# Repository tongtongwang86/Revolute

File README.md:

# Revolute
- nRF52833 Based Scroll wheel dial

## Introducing Revolute
 <a href="https://tongtonginc.com/revolute">Visit the product page website (Faster loading time, Interactive 3D Models, Demo Videos)</a>

### The Revolute is a scroll wheel/dial that aims to revolutionize the way we interact with complex software applications.

- Revolute currently simulate keyboard inputs, consumer controlls, mouse inputs.

- the actions and sensitivity of the wheel can be configured through the revolute configurator app that will be available for iOS, Macos and Windows devices that have bluetooth support.

- Configuratios done on revolute is persistently stored on device, which means that revolute can work on any device with Bluetooth and HID support.

- Revolute has a number of use cases and is not limited to: scrubbing through a timeline in a video editing app, changing the brush size in 3D/2D painting, smooth scrolling, volume controll, brightness control, media playback control, quickly pressing keys in short successions within games. if you get two you can bind each revolute axis to x and y of the cursor, making a etch a sketch

- Gamepad emulation is currently in development, which will allow you to use revolute within a wide range of mobile and console games.

## How the Revolute works

### Rotational inputs

- Revolute has gone through a number of iterations and currently uses the AS5600 magnetic encoder. It recordes the angle of a diametric magnet embedded within the base of the revolute, which the SoC will process and send bluetooth reports to the host device.

### BLE connection

- Using BLE wireless connection we can have the Revolute connected to devices such as your computer, phone, or tablet using bluetooth. 
- By using the nRF52833 SoC and Zephyr RTOS, the Revolute is designed to maximize its power efficiency for bluetooth functionalities.

### Central button
- By pressing down on the Revolute, it powers on the device.
- After powering on the device, the button can also be configured to other actions based on your configurations
- Power it off by pressing and holding down on the button.

### Configuration

- As mentioned before, the Revolute's functionalities can be configured through the Revolute Configuration app that is currently in development
- Once you have made your changes to our configurations, they are then sent to the Revolute over bluetooth and stored locally on the SoC. allowing you to use the same configurations across different devices.

### Accessories 
- Revolute has a range of existing accessories that allow you to use it within different use cases

- Key attachment 

- Adhesive/magnetic attachment

- Phone attachment 

- Revo-Pod charges the revolute and is a place to store your attachments.

- The attachment can be hot swapped with a common bearing interface.

### Charging and Battery Replacement
- For this device to be wireless, the Revolute is comprised of a 70Mah li-Ion rechargable coin cell battery (LIR2032H)
- The Revolute uses the BQ24075-RGT charger ic and BQ27441-G1 fuel gauge, both by Texas Instruments, for charging, monitoring, and managing the battery that powers the system.
- To charge the Revolute, simply take your Revopod and mount it in the pod and have the two pogopins aligned with the receptors on the wheel.
- To replace the battery, simply flip the Revolute over, press it down until you feel the central button being completely pressed down, and twist it clockwise and you should be able to have the entire Revolute disassembled. From there, simply place a new battery in and reverse the steps of how you disassembled it after your align the cap with the body chassis.

### *Gyro mouse
- With the LSM6DS3 gyroscope accelerometer incorporated in on the Revolute, you can configure it to control the movements of your cursor by moving the Revolute around.
- This feature is still in development and will be finalized shortly in our next firmware updates

## How this repo works
- PCB hardware files are in the folder /Hardware
- 3D printed part files are stored in the folder /3D Prints
- Latest firmware is hosted on the repo <a href="https://github.com/tongtongwang86/revolute-firmware-ci">"revolute-firmware-ci"</a>
- There is also a wired version of the revolute in this repo

## Get your own Revolute
- Revolute is still in development and will be ready soon

 - <a href="https://tongtonginc.com/revolute">For more information head to the product page</a>

- Feel free to DM us if you have any questions or requests

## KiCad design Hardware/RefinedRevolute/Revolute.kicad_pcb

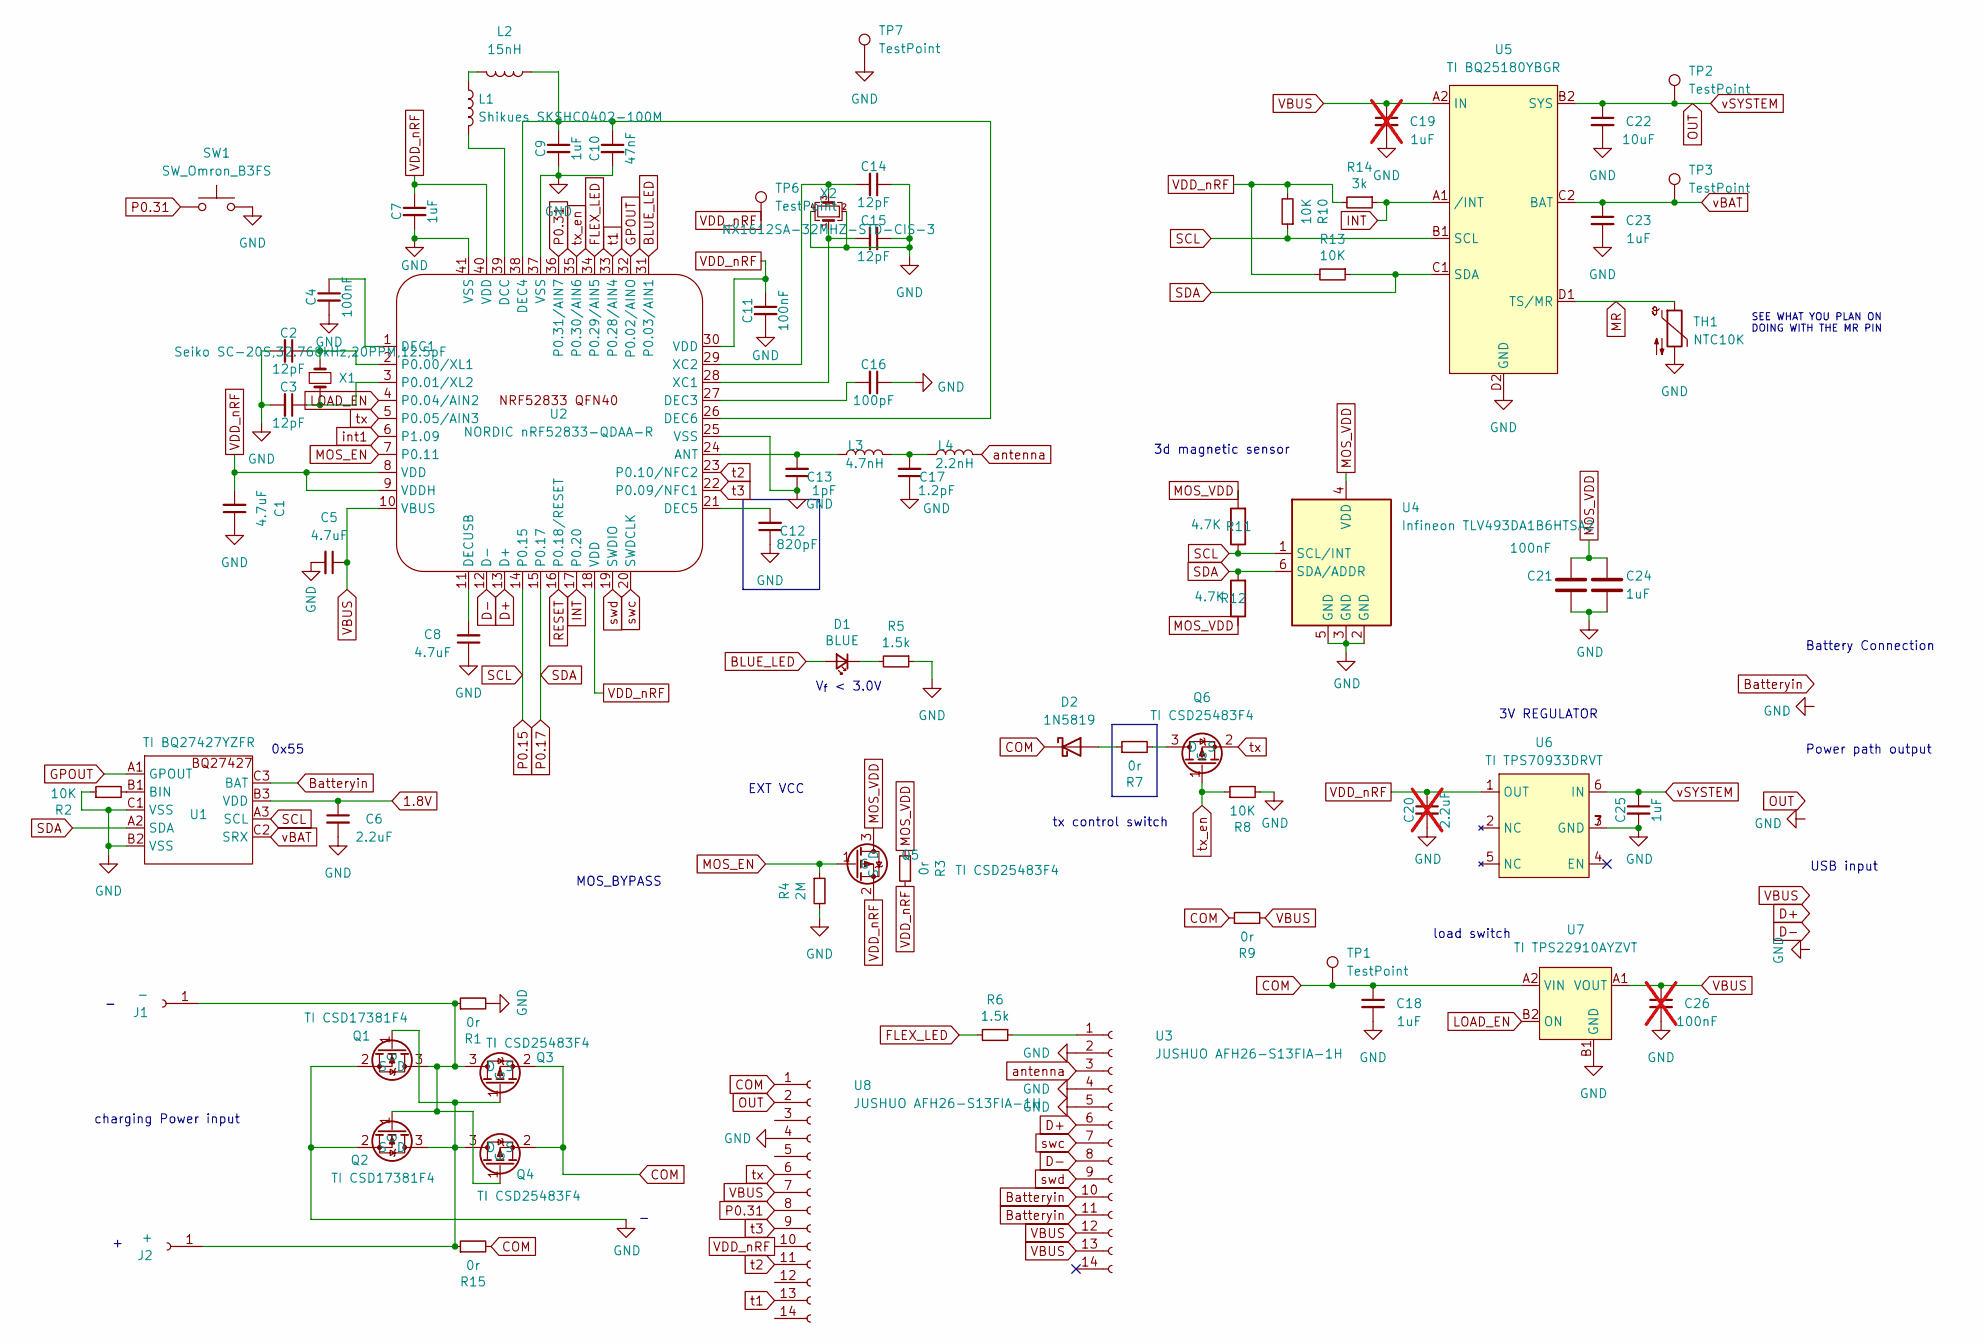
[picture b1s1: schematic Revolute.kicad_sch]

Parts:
C1, C5, C8: 4.7uF; C_0402_1005Metric
C2, C3, C14, C15: 12pF; C_0402_1005Metric
C4, C11, C21: 100nF; C_0402_1005Metric
C6: 2.2uF; C_0402_1005Metric
C7, C9, C18, C23, C24, C25: 1uF; C_0402_1005Metric
C10: 47nF; C_0402_1005Metric
C12: 820pF; C_0402_1005Metric
C13: 1pF; C_0402_1005Metric
C16: 100pF; C_0402_1005Metric
C17: 1.2pF; C_0402_1005Metric
C19: 1uF; C_0402_1005Metric; not fitted
C20: 2.2uF; C_0603_1608Metric; not fitted
C22: 10uF; C_0402_1005Metric
C26: 100nF; C_0402_1005Metric; not fitted
D1: BLUE; LED_0402_1005Metric
D2: 1N5819; D_SOD-523
J1: -; Pogo-pin-recepticle
J2: +; Pogo-pin-recepticle
L1: Shikues SKSHC0402-100M; L_0402_1005Metric; LCSC C18212629
L2: 15nH; L_0402_1005Metric
L3: 4.7nH; L_0402_1005Metric
L4: 2.2nH; L_0402_1005Metric
Q1, Q2: TI CSD17381F4; Mosfet0402; LCSC C2869182
Q3, Q4, Q5, Q6: TI CSD25483F4; Mosfet0402; LCSC C485542
R1, R3, R7, R9, R15: 0r; R_0402_1005Metric
R2, R8, R10, R13: 10K; R_0402_1005Metric
R4: 2M; R_0402_1005Metric
R5, R6: 1.5k; R_0402_1005Metric
R11, R12: 4.7K; R_0402_1005Metric
R14: 3k; R_0402_1005Metric
SW1: SW_Omron_B3FS; 16mmCompButton
TH1: NTC10K; R_0402_1005Metric; LCSC C77131
TP1, TP2, TP3, TP6, TP7: TestPoint; TestPoint_Pad_D1.0mm
U1: TI BQ27427YZFR; Texas_DSBGA-9_1.62mmx1.58mm_Layout3x3_P0.5mm; LCSC C6075475
U2: NORDIC nRF52833-QDAA-R; nrf52833; LCSC C2895249
U3, U8: JUSHUO AFH26-S13FIA-1H; FPC; LCSC C5139786
U4: Infineon TLV493DA1B6HTSA2; SOT-23-6-Small; LCSC C126688
U5: TI BQ25180YBGR; Texas_DSBGA-8_0.705x1.468mm_Layout2x4_P0.4mm; LCSC C3682423
U6: TI TPS70933DRVT; DRV 6PIN; LCSC C2861809
U7: TI TPS22910AYZVT; BGA4N50P2X2_88X88X50N; LCSC C2150034
X1: Seiko SC-20S,32.768kHz,20PPM,12.5pF; Crystal_SMD_2012-2Pin_2.0x1.2mm; LCSC C97607
X2: NX1612SA-32MHZ-STD-CIS-3; Crystal_SMD_2016-4Pin_2.0x1.6mm

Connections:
1.8V: C6.1, U1.B3 (VDD)
BLUE_LED: D1.2 (A), U2.31 (P0.03/AIN1)
Batteryin: U1.C3 (BAT), U3.10, U3.11
COM: C18.1, D2.1 (K), Q3.2 (S), Q4.2 (S), R9.1, R15.2, TP1.1, U7.A2 (VIN), U8.1
D+: U2.13 (D+), U3.6
D-: U2.12 (D-), U3.8
FLEX_LED: R6.2, U2.34 (P0.29/AIN5)
GND: C1.1, C2.2, C3.2, C4.2, C5.2, C6.2, C7.2, C8.1, C9.2, C10.2, C11.2, C12.1, C13.1, C14.1, C15.1, C16.1, C17.1, C18.2, C19.2, C20.2, C21.2, C22.2, C23.2, C24.2, C25.2, C26.2, Q1.2 (S), Q2.2 (S), R1.2, R2.1, R4.2, R5.1, R8.2, SW1.2, TH1.2, TP7.1, U1.B2 (VSS), U1.C1 (VSS), U2.25 (VSS), U2.37 (VSS), U2.41 (VSS), U3.2, U3.4, U3.5, U4.2 (GND), U4.3 (GND), U4.5 (GND), U5.D2 (GND), U6.3 (GND), U6.7 (GND), U7.B1 (GND), U8.4, X2.2, X2.4
GPOUT: U1.A1 (GPOUT), U2.32 (P0.02/AINO)
INT: R14.1, U2.17 (P0.20), U5.A1 (/INT)
LOAD_EN: U2.4 (P0.04/AIN2), U7.B2 (ON)
MOS_EN: Q5.1 (G), R4.1, U2.7 (P0.11)
MOS_VDD: C21.1, C24.1, Q5.3 (D), R3.2, R11.2, R12.1, U4.4 (VDD)
MR: TH1.1, U5.D1 (TS/MR)
unnamed: C17.2, L3.2, L4.1
unnamed: D1.1 (K), R5.2
unnamed: D2.2 (A), R7.1
unnamed: J1.1, Q1.3 (D), Q2.1 (G), Q3.3 (D), Q4.1 (G), R1.1
unnamed: J2.1, Q1.1 (G), Q2.3 (D), Q3.1 (G), Q4.3 (D), R15.1
unnamed: L1.1, L2.2
unnamed: Q6.3 (D), R7.2
unnamed: R2.2, U1.B1 (BIN)
unnamed: C13.2, L3.1, U2.24 (ANT)
unnamed: L1.2, U2.39 (DCC)
unnamed: C4.1, U2.1 (DEC1)
unnamed: C16.2, U2.27 (DEC3)
unnamed: C9.1, C10.1, L2.1, U2.26 (DEC6), U2.38 (DEC4)
unnamed: C12.2, U2.21 (DEC5)
unnamed: C8.2, U2.11 (DECUSB)
unnamed: C2.1, U2.2 (P0.00/XL1), X1.1
unnamed: C3.1, U2.3 (P0.01/XL2), X1.2
unnamed: C15.2, U2.28 (XC1), X2.1
unnamed: C14.2, U2.29 (XC2), X2.3
unnamed: R6.1, U3.1
OUT: C22.1, C25.1, TP2.1, U5.B2 (SYS), U6.6 (IN), U8.2
P0.15: R10.1, R11.1, U1.A3 (SCL), U2.14 (P0.15), U4.1 (SCL/INT), U5.B1 (SCL)
P0.17: R12.2, R13.1, U1.A2 (SDA), U2.15 (P0.17), U4.6 (SDA/ADDR), U5.C1 (SDA)
P0.31: SW1.1, U2.36 (P0.31/AIN7), U8.8
RESET: U2.16 (P0.18/RESET)
VBUS: C5.1, C19.1, C26.1, R9.2, U2.10 (VBUS), U3.12, U3.13, U5.A2 (IN), U7.A1 (VOUT), U8.7
VDD_nRF: C1.2, C7.1, C11.1, C20.1, Q5.2 (S), R3.1, R10.2, R13.2, R14.2, TP6.1, U2.8 (VDD), U2.9 (VDDH), U2.18 (VDD), U2.30 (VDD), U2.40 (VDD), U6.1 (OUT), U8.10
antenna: L4.2, U3.3
int1: U2.6 (P1.09)
swc: U2.20 (SWDCLK), U3.7
swd: U2.19 (SWDIO), U3.9
t1: U2.33 (P0.28/AIN4), U8.13
t2: U2.23 (P0.10/NFC2), U8.11
t3: U2.22 (P0.09/NFC1), U8.9
tx: Q6.2 (S), U2.5 (P0.05/AIN3), U8.6
tx_en: Q6.1 (G), R8.1, U2.35 (P0.30/AIN6)
vBAT: C23.1, TP3.1, U1.C2 (SRX), U5.C2 (BAT)

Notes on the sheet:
3d magnetic sensor
SEE WHAT YOU PLAN ON DOING WITH THE MR PIN
Battery Connection
EXT VCC
Power path output
V_{f} < 3.0V
0x55
charging Power input
USB input
load switch
MOS_BYPASS
tx control switch
3V REGULATOR

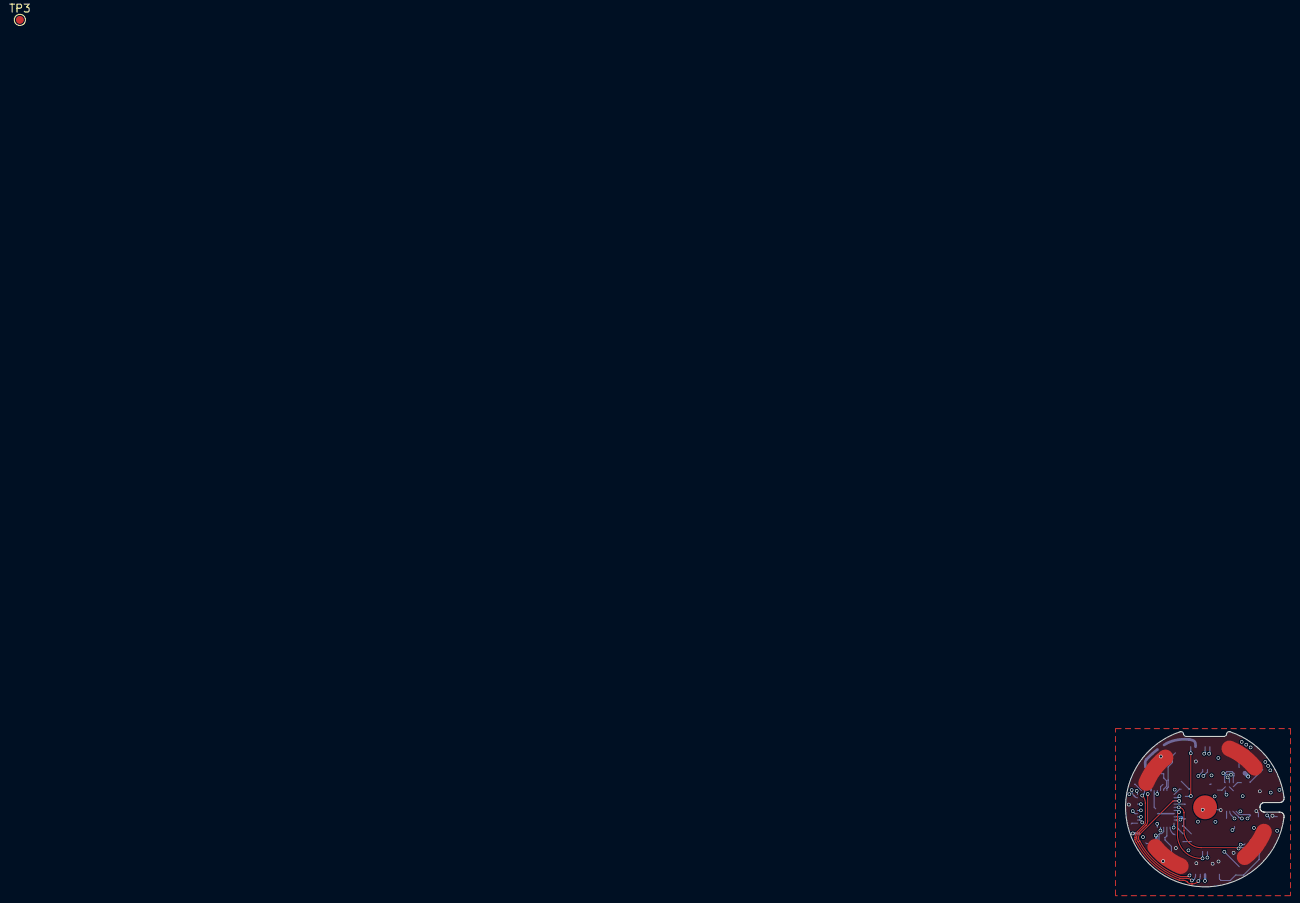
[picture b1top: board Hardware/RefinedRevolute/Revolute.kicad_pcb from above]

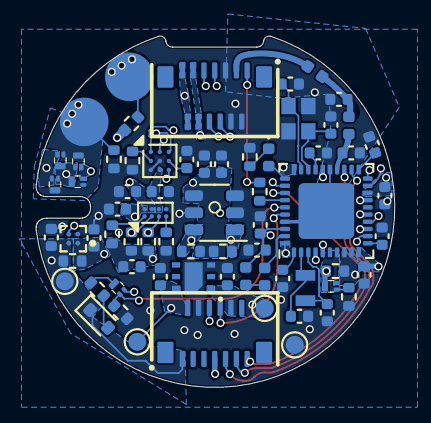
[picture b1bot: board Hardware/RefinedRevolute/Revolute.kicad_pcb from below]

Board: 4 copper layers, 19.9 x 19.5 mm, 71 parts (69 on the bottom side), 49 nets.

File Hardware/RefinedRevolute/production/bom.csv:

Designator,Footprint,Quantity,Value,LCSC Part #
"C1, C5, C8",0402,3,4.7uF,
C10,0402,1,47nF,
"C11, C21, C26, C4",0402,4,100nF,
C12,0402,1,820pF,
C13,0402,1,1pF,
"C14, C15, C2, C3",0402,4,12pF,
C16,0402,1,100pF,
C17,0402,1,1.2pF,
"C18, C19, C23, C24, C25, C7, C9",0402,7,1uF,
C22,0402,1,10uF,
C6,0402,1,2.2uF,
D1,0402,1,BLUE,
D2,D_SOD-523,1,1N5819,
J1,Pogo-pin-recepticle,1,-,
J2,Pogo-pin-recepticle,1,+,
L1,0402,1,10uH,
L2,0402,1,15nH,
L3,0402,1,4.7nH,
L4,0402,1,2.2nH,
"Q1, Q2",Mosfet0402,2,TI CSD17381F4,C2869182
"Q3, Q4, Q5, Q6",Mosfet0402,4,TI CSD25483F4,C485542
"R1, R15, R3, R7, R9",0402,5,0r,
"R10, R13, R2, R8",0402,4,10K,
"R11, R12",0402,2,4.7K,
R14,0402,1,3k,
R4,0402,1,2M,
"R5, R6",0402,2,1.5k,
SW1,16mmCompButton,1,SW_Omron_B3FS,
TH1,0402,1,NTC10K,C77131
"TP1, TP2, TP6, TP7",TestPoint_Pad_D1.0mm,4,TestPoint,
U1,Texas_DSBGA-9_1.62mmx1.58mm_Layout3x3_P0.5mm,1,TI BQ27427YZFR,C6075475
U2,nrf52833,1,NORDIC nRF52833-QDAA-R,C2895249
"U3, U8",FPC,2,JUSHUO AFH26-S13FIA-1H,C5139786
U4,SOT-23-6-Small,1,Infineon TLV493DA1B6HTSA2,C126688
U5,Texas_DSBGA-8_0.705x1.468mm_Layout2x4_P0.4mm,1,TI BQ25180YBGR,C3682423
U6,DRV 6PIN,1,TI TPS70933DRVT,C2861809
U7,BGA4N50P2X2_88X88X50N,1,TI TPS22910AYZVT,C2150034
X1,Crystal_SMD_2012-2Pin_2.0x1.2mm,1,32.768 kHz,
X2,Crystal_SMD_2016-4Pin_2.0x1.6mm,1,32MHZ,

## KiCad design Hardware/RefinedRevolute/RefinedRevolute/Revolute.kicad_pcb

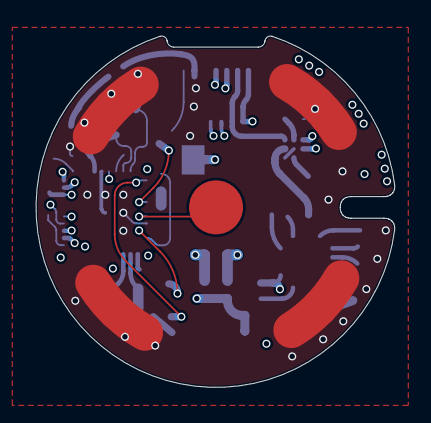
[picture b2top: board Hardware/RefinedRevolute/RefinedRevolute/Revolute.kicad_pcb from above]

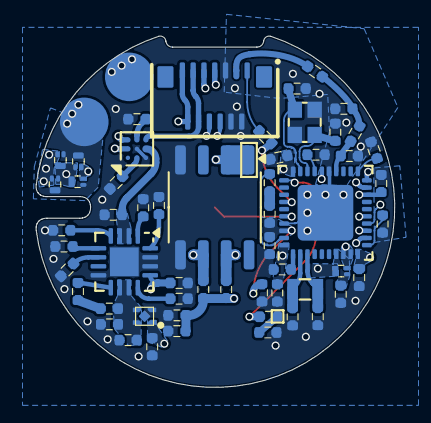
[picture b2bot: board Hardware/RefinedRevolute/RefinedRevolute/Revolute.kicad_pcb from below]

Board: 4 copper layers, 19.9 x 19.5 mm, 59 parts (58 on the bottom side), 45 nets.

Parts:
C1, C5, C7: 4.7uF; 0402
C2, C3, C14, C15: 12pF; 0402
C4, C11, C28: 100nF; 0402
C6, C9, C20, C21, C23, C27: 1uF; 0402
C8: 2.2uF; 0402
C10: 47nF; 0402
C12: 820pF; 0402
C13: 1pF; 0402
C16: 100pF; 0402
C17: 1.2pF; 0402
C22, C24: 10uF; 0402
D1: BLUE; 0402
D2: LED; 0402
J1: -; Pogo-pin-recepticle
J2: +; Pogo-pin-recepticle
L1: 10uH; 0402
L2: 15nH; 0402
L3: 4.7nH; 0402
L4: 2.2nH; 0402
Q1, Q2: NMOS-CSD17381F4; Mosfet0402
Q3, Q4, Q5: PMOS-CSD25483F4; Mosfet0402
R1: 10k; 0402
R2: 2M; 0402
R3, R11, R12: 1.5k; 0402
R4: 100K; 0402
R5: 1.1k; 0402
R6: 590; 0402
R7, R8: 0Ω; 0402
R9, R10: 4.7K; 0402
SW1: SW_Omron_B3FS; 16mmCompButton
TH1: 10K; 0402
U5: BQ27427; Texas_DSBGA-9_1.62mmx1.58mm_Layout3x3_P0.5mm
U6: nrf52833_qfn40; nrf52833
U8: Conn_01x14_Socket; FPC
U9: AS5600; SOIC-8-1EP_3.9x4.9mm_P1.27mm_EP2.514x3.2mm
U10: BQ24075RGT; VQFN-16-1EP_3x3mm_P0.5mm_EP1.6x1.6mm
U11: MIC5504; TDFN-4
X1: 32.768 kHz; Crystal_SMD_2012-2Pin_2.0x1.2mm
X2: 32MHZ; Crystal_SMD_2016-4Pin_2.0x1.6mm

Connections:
1.8V: C8.1, U5.B3 (VDD)
BLUE_LED: D1.2 (A), U6.31 (P0.03/AIN1)
Batteryin: U5.C3 (BAT), U8.10, U8.11
CE: R4.1, U10.4 (~CE)
D+: U6.13 (D+), U8.6
D-: U6.12 (D-), U8.8
FLEX_LED: R12.2, U6.34 (P0.29/AIN5)
GND: C1.1, C2.2, C3.2, C4.2, C5.2, C6.2, C7.1, C8.2, C9.2, C10.2, C11.2, C12.1, C13.1, C14.1, C15.1, C16.1, C17.1, C20.2, C21.2, C22.1, C23.2, C24.2, C27.2, C28.2, Q1.2 (S), Q2.2 (S), R1.1, R2.2, R3.1, R4.2, R5.2, R6.2, R7.1, R8.1, SW1.2, TH1.2, U5.B2 (VSS), U5.C1 (VSS), U6.25 (VSS), U6.37 (VSS), U6.41 (VSS), U8.2, U8.4, U8.5, U9.4 (GND), U9.5 (PGO), U10.8 (VSS), U10.14 (TMR), U10.15 (SYSOFF), U10.17 (VSS), U11.2 (GND), U11.5 (GND), X2.2, X2.4
MOS_EN: Q3.1 (G), R2.1, U6.7 (P0.11)
MOS_VDD: C27.1, C28.1, Q3.3 (D), R9.1, R10.2, U9.1 (VDD5V), U9.2 (VDD3V3)
unnamed: C17.2, L3.2, L4.1
unnamed: D1.1 (K), R3.2
unnamed: D2.1 (K), R11.2
unnamed: J1.1, Q1.3 (D), Q2.1 (G), Q4.3 (D), Q5.1 (G)
unnamed: J2.1, Q1.1 (G), Q2.3 (D), Q4.1 (G), Q5.3 (D)
unnamed: L1.1, L2.2
unnamed: R1.2, U5.B1 (BIN)
unnamed: C13.2, L3.1, U6.24 (ANT)
unnamed: L1.2, U6.39 (DCC)
unnamed: C4.1, U6.1 (DEC1)
unnamed: C16.2, U6.27 (DEC3)
unnamed: C9.1, C10.1, L2.1, U6.26 (DEC6), U6.38 (DEC4)
unnamed: C12.2, U6.21 (DEC5)
unnamed: C7.2, U6.11 (DECUSB)
unnamed: C2.1, U6.2 (P0.00/XL1), X1.1
unnamed: C3.1, U6.3 (P0.01/XL2), X1.2
unnamed: C15.2, U6.28 (XC1), X2.1
unnamed: C14.2, U6.29 (XC2), X2.3
unnamed: R12.1, U8.1
unnamed: R7.2, U10.6 (EN1)
unnamed: R8.2, U10.5 (EN2)
unnamed: R5.1, U10.12 (ILIM)
unnamed: R6.1, U10.16 (ISET)
unnamed: TH1.1, U10.1 (TS)
unnamed: R11.1, U10.9 (~CHG)
OUT: C20.1, C24.1, D2.2 (A), U10.10 (OUT), U10.11 (OUT), U11.3 (EN), U11.4 (VIN)
P0.15: R9.2, U5.A3 (SCL), U6.14 (P0.15), U9.7 (SCL)
P0.17: R10.1, U5.A2 (SDA), U6.15 (P0.17), U9.6 (SDA)
P0.31: SW1.1, U6.36 (P0.31/AIN7)
VBUS: C5.1, C21.1, Q4.2 (S), Q5.2 (S), U6.10 (VBUS), U8.12, U8.13, U10.13 (IN)
VDD_nRF: C1.2, C6.1, C11.1, C23.1, Q3.2 (S), U6.8 (VDD), U6.9 (VDDH), U6.18 (VDD), U6.30 (VDD), U6.40 (VDD), U11.1 (VOUT)
antenna: L4.2, U8.3
swc: U6.20 (SWDCLK), U8.7
swd: U6.19 (SWDIO), U8.9
vBAT: C22.2, U5.C2 (SRX), U10.2 (BAT), U10.3 (BAT)

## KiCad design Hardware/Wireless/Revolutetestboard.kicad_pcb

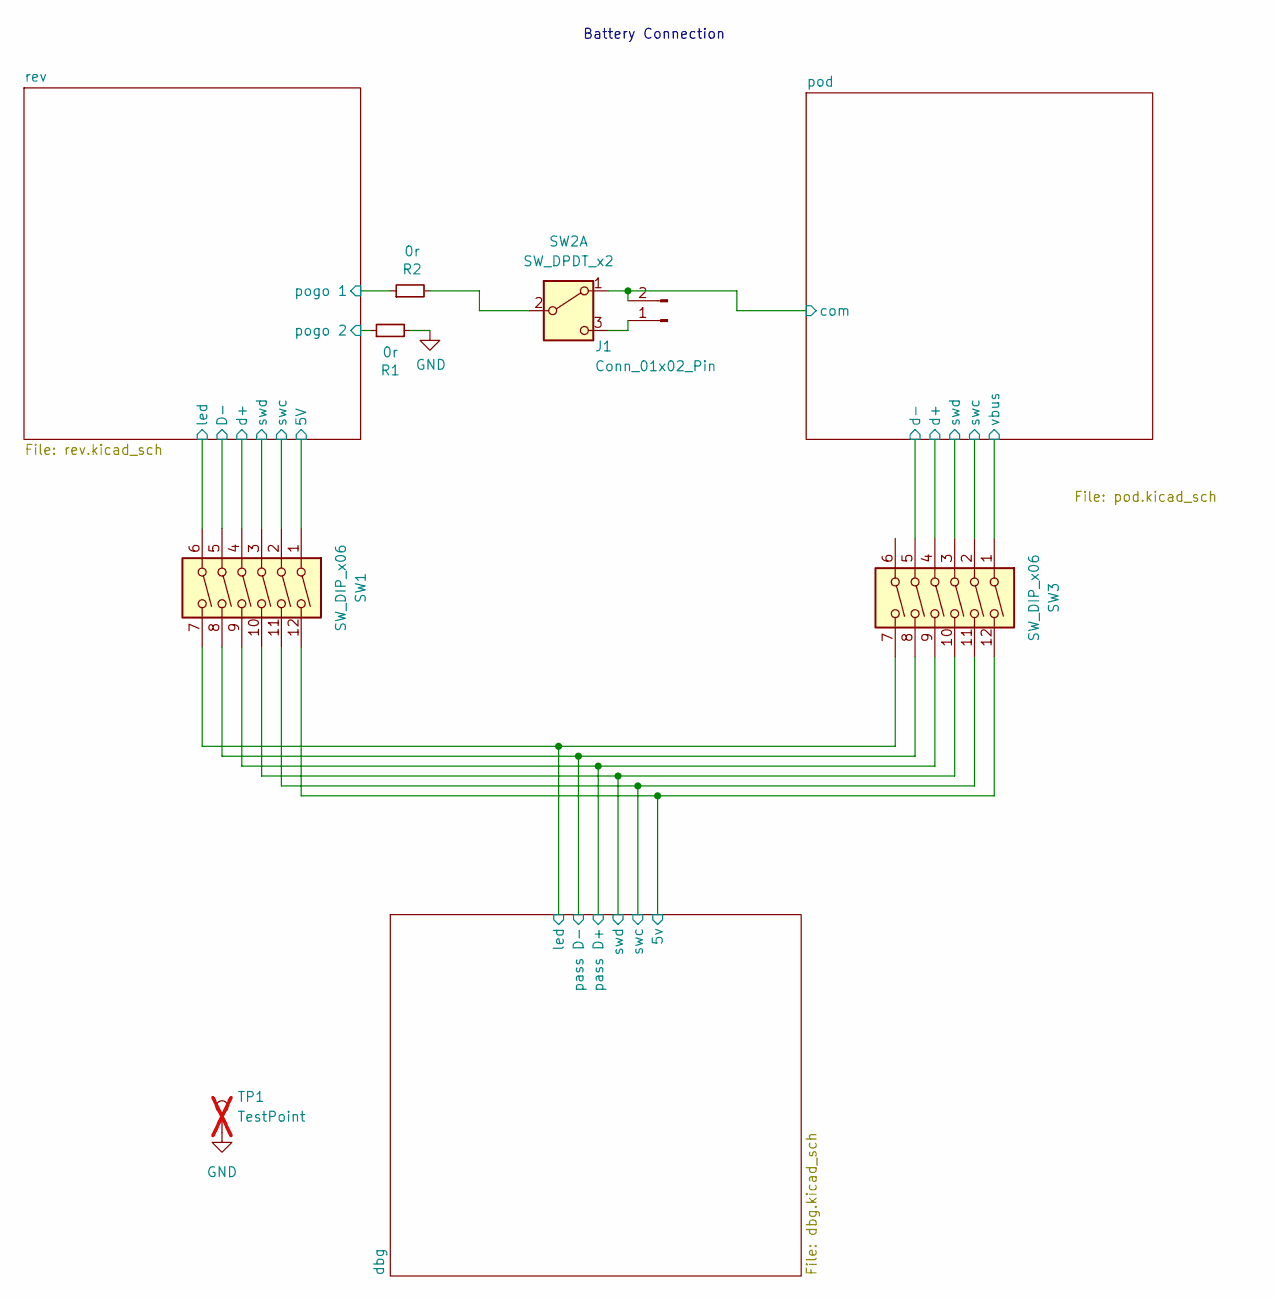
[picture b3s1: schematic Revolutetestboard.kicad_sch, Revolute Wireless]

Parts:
J1: Conn_01x02_Pin; PinHeader_1x02_P2.54mm_Vertical
R1, R2: 0r; 0402
SW1, SW3: SW_DIP_x06; SW_DIP_SPSTx06_Slide_Copal_CHS-06B_W7.62mm_P1.27mm
SW2: SW_DPDT_x2; MST-12C05 SLIDEBUTTON
TP1: TestPoint; TestPoint_Pad_D1.0mm; not fitted

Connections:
5V(2): SW1.12, SW3.12; also elsewhere on the board
/dbg/USBDM2: SW1.8, SW3.8; also elsewhere on the board
/dbg/USBDP2: SW1.9, SW3.9; also elsewhere on the board
/dbg/swc: SW1.11, SW3.11; also elsewhere on the board
/dbg/swd: SW1.10, SW3.10; also elsewhere on the board
/pod/COM: J1.2, SW2.1 (A); also elsewhere on the board
/pod/D+: SW3.4; also elsewhere on the board
/pod/D-: SW3.5; also elsewhere on the board
/pod/VBUS: SW3.1; also elsewhere on the board
/pod/swc: SW3.2; also elsewhere on the board
/pod/swd: SW3.3; also elsewhere on the board
/rev/+: R1.1; also elsewhere on the board
/rev/-: R2.1; also elsewhere on the board
/rev/D+: SW1.4; also elsewhere on the board
/rev/D-: SW1.5; also elsewhere on the board
/rev/FLEX_LED: SW1.6; also elsewhere on the board
/rev/VBUS: SW1.1; also elsewhere on the board
/rev/swc: SW1.2; also elsewhere on the board
/rev/swd: SW1.3; also elsewhere on the board
GND: R1.2, TP1.1; also elsewhere on the board
unnamed: J1.1, SW2.3 (C)
unnamed: R2.2, SW2.2 (B)
led: SW1.7, SW3.7; also elsewhere on the board

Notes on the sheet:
Battery Connection

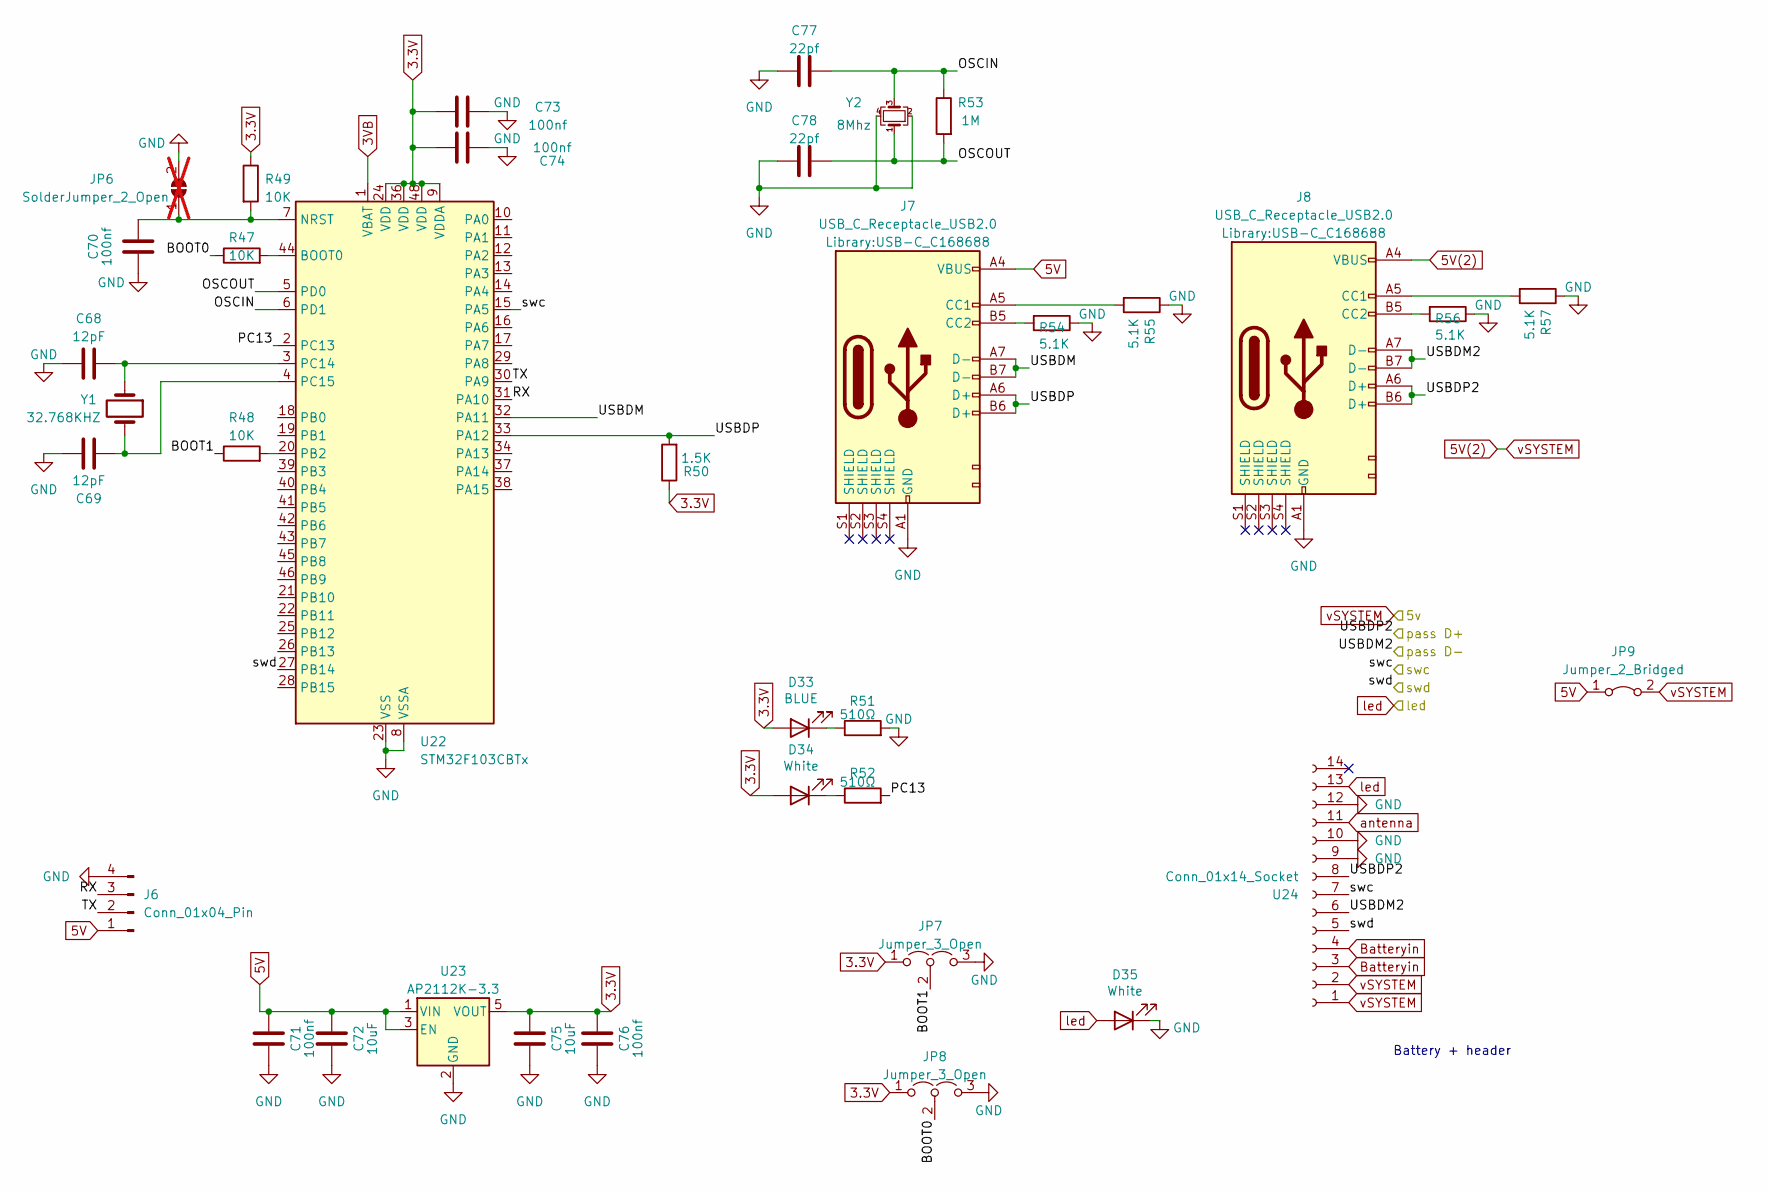
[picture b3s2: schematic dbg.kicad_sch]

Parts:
C68, C69: 12pF; 0402
C70, C71, C73, C74, C76: 100nf; 0402
C72, C75: 10uF; 0402
C77, C78: 22pf; 0402
D33: BLUE; LED_0402_1005Metric
D34, D35: White; LED_0402_1005Metric
J6: Conn_01x04_Pin; PinHeader_1x04_P1.27mm_Vertical
J7, J8: USB_C_Receptacle_USB2.0; USB-C_C168688
JP6: SolderJumper_2_Open; SolderBridge; not fitted
JP7, JP8: Jumper_3_Open; SolderJumper-3_P1.3mm_Open_RoundedPad1.0x1.5mm
JP9: Jumper_2_Bridged; SolderJumper-2_P1.3mm_Bridged_RoundedPad1.0x1.5mm
R47, R48, R49: 10K; 0402
R50: 1.5K; R_0402_1005Metric
R51, R52: 510Ω; R_0402_1005Metric
R53: 1M; R_0402_1005Metric
R54, R55, R56, R57: 5.1K; R_0402_1005Metric
U22: STM32F103CBTx; LQFP-48_7x7mm_P0.5mm
U23: AP2112K-3.3; SOT-23-5
U24: Conn_01x14_Socket; FPC
Y1: 32.768KHZ; Crystal_SMD_3215-2Pin_3.2x1.5mm
Y2: 8Mhz; Crystal_SMD_3225-4Pin_3.2x2.5mm

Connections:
3.3V: C73.2, C74.2, C75.2, C76.2, D33.2 (A), D34.2 (A), JP7.1 (A), JP8.1 (A), R49.1, R50.1, U22.9 (VDDA), U22.24 (VDD), U22.36 (VDD), U22.48 (VDD), U23.5 (VOUT)
3VB: U22.1 (VBAT)
5V: C71.2, C72.2, J6.1, J7.A4 (VBUS), JP9.1 (A), U23.1 (VIN), U23.3 (EN)
5V(2): J8.A4 (VBUS), JP9.2 (B), U24.1, U24.2; also elsewhere on the board
/dbg/BOOT0: JP8.2 (C), R47.1
/dbg/BOOT1: JP7.2 (C), R48.1
/dbg/OSCIN: C77.2, R53.1, U22.6 (PD1), Y2.3
/dbg/OSCOUT: C78.2, R53.2, U22.5 (PD0), Y2.1
/dbg/PC13: R52.2, U22.2 (PC13)
/dbg/RX: J6.3, U22.31 (PA10)
/dbg/TX: J6.2, U22.30 (PA9)
/dbg/USBDM: J7.A7 (D-), J7.B7 (D-), U22.32 (PA11)
/dbg/USBDM2: J8.A7 (D-), J8.B7 (D-), U24.6; also elsewhere on the board
/dbg/USBDP: J7.A6 (D+), J7.B6 (D+), R50.2, U22.33 (PA12)
/dbg/USBDP2: J8.A6 (D+), J8.B6 (D+), U24.8; also elsewhere on the board
/dbg/swc: U22.15 (PA5), U24.7; also elsewhere on the board
/dbg/swd: U22.27 (PB14), U24.5; also elsewhere on the board
Batteryin: U24.3, U24.4
GND: C68.1, C69.2, C70.1, C71.1, C72.1, C73.1, C74.1, C75.1, C76.1, C77.1, C78.1, D35.1 (K), J6.4, J7.A1 (GND), J8.A1 (GND), JP6.2 (B), JP7.3 (B), JP8.3 (B), R51.2, R54.1, R55.1, R56.1, R57.1, U22.8 (VSSA), U22.23 (VSS), U22.35 (VSS), U22.47 (VSS), U23.2 (GND), U24.9, U24.10, U24.12, Y2.2, Y2.4; also elsewhere on the board
unnamed: D33.1 (K), R51.1
unnamed: D34.1 (K), R52.1
unnamed: J7.A5 (CC1), R55.2
unnamed: J7.B5 (CC2), R54.2
unnamed: J8.A5 (CC1), R57.2
unnamed: J8.B5 (CC2), R56.2
unnamed: C70.2, JP6.1 (A), R49.2, U22.7 (NRST)
unnamed: R47.2, U22.44 (BOOT0)
unnamed: R48.2, U22.20 (PB2)
unnamed: C68.2, U22.3 (PC14), Y1.1
unnamed: C69.1, U22.4 (PC15), Y1.2
antenna: U24.11
led: D35.2 (A), U24.13; also elsewhere on the board

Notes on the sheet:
Battery + header
